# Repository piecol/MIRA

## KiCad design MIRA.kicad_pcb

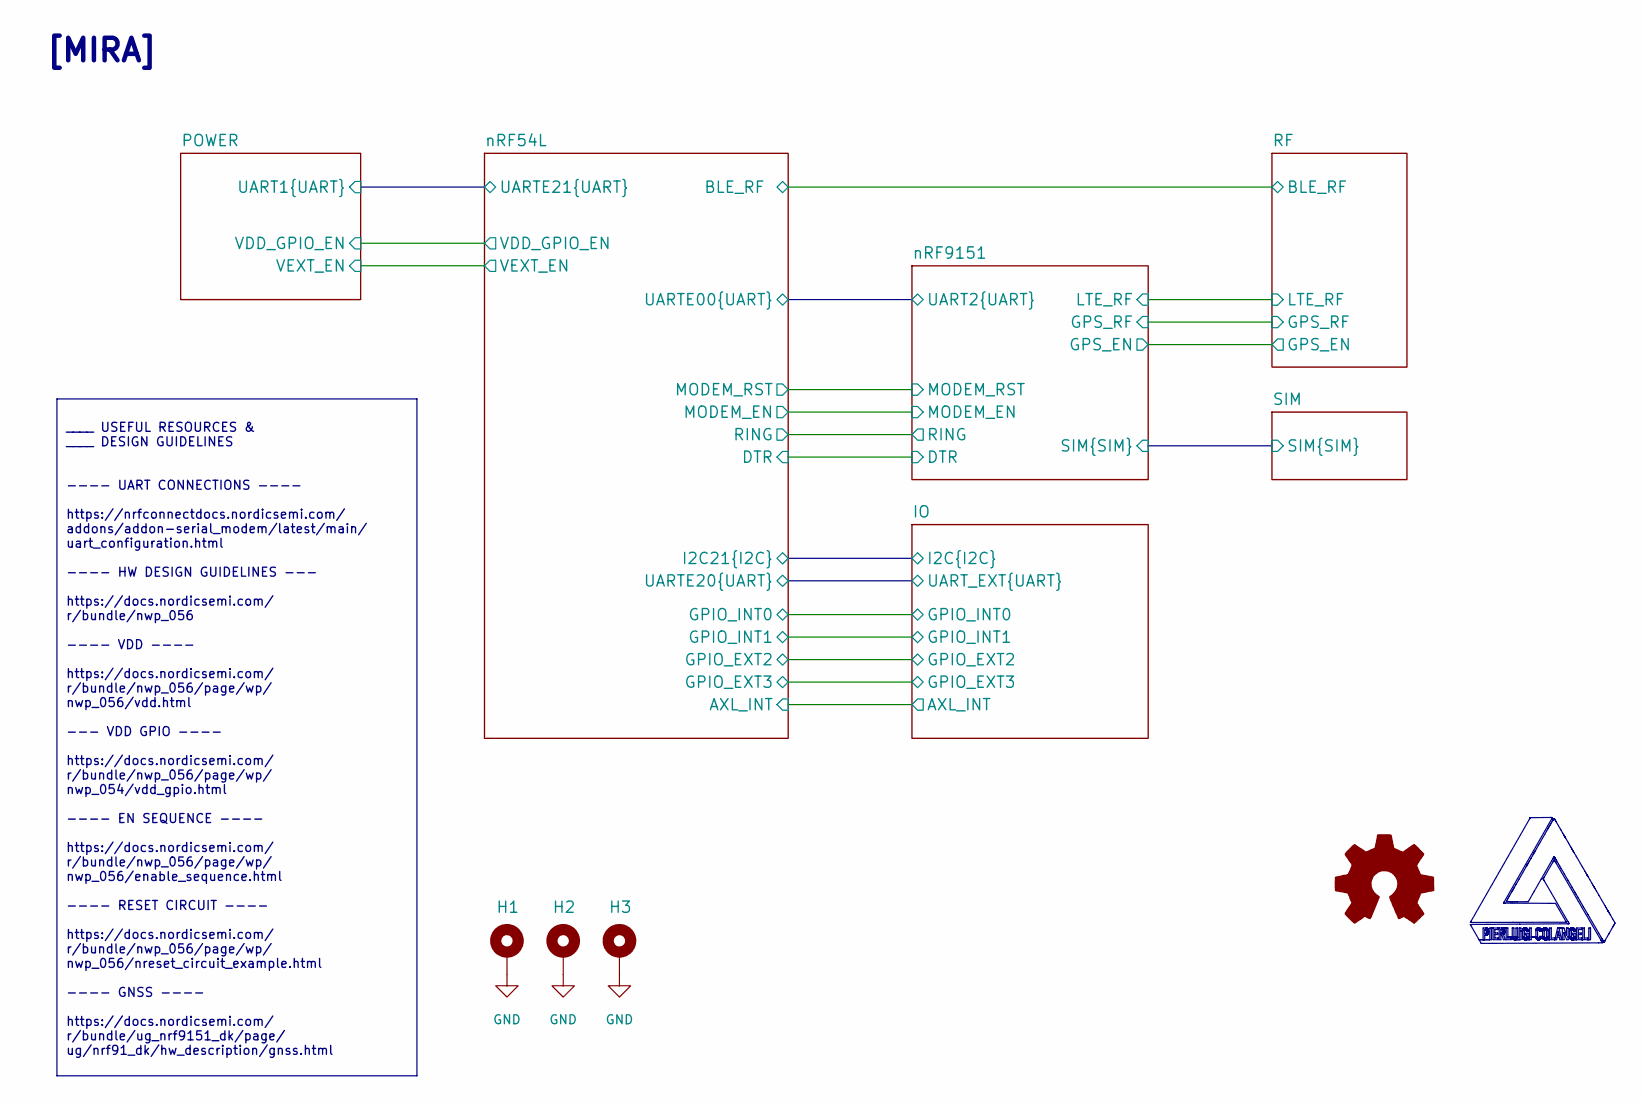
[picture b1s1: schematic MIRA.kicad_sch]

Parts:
H1, H2, H3: MountingHole_Pad; MountingHole_2.2mm_M2_ISO7380_Pad

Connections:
GND: H1.1 (1_1), H2.1 (1_1), H3.1 (1_1); also elsewhere on the board

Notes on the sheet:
[MIRA]
____ USEFUL RESOURCES & ____ DESIGN GUIDELINES ---- UART CONNECTIONS ---- https://nrfconnectdocs.nordicsemi.com/ addons/addon-serial_modem/latest/main/ uart_configuration.html ---- HW DESIGN GUIDELINES --- https://docs.nordicsemi.com/ r/bundle/nwp_056 ---- VDD ---- https://docs.nordicsemi.com/ r/bu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

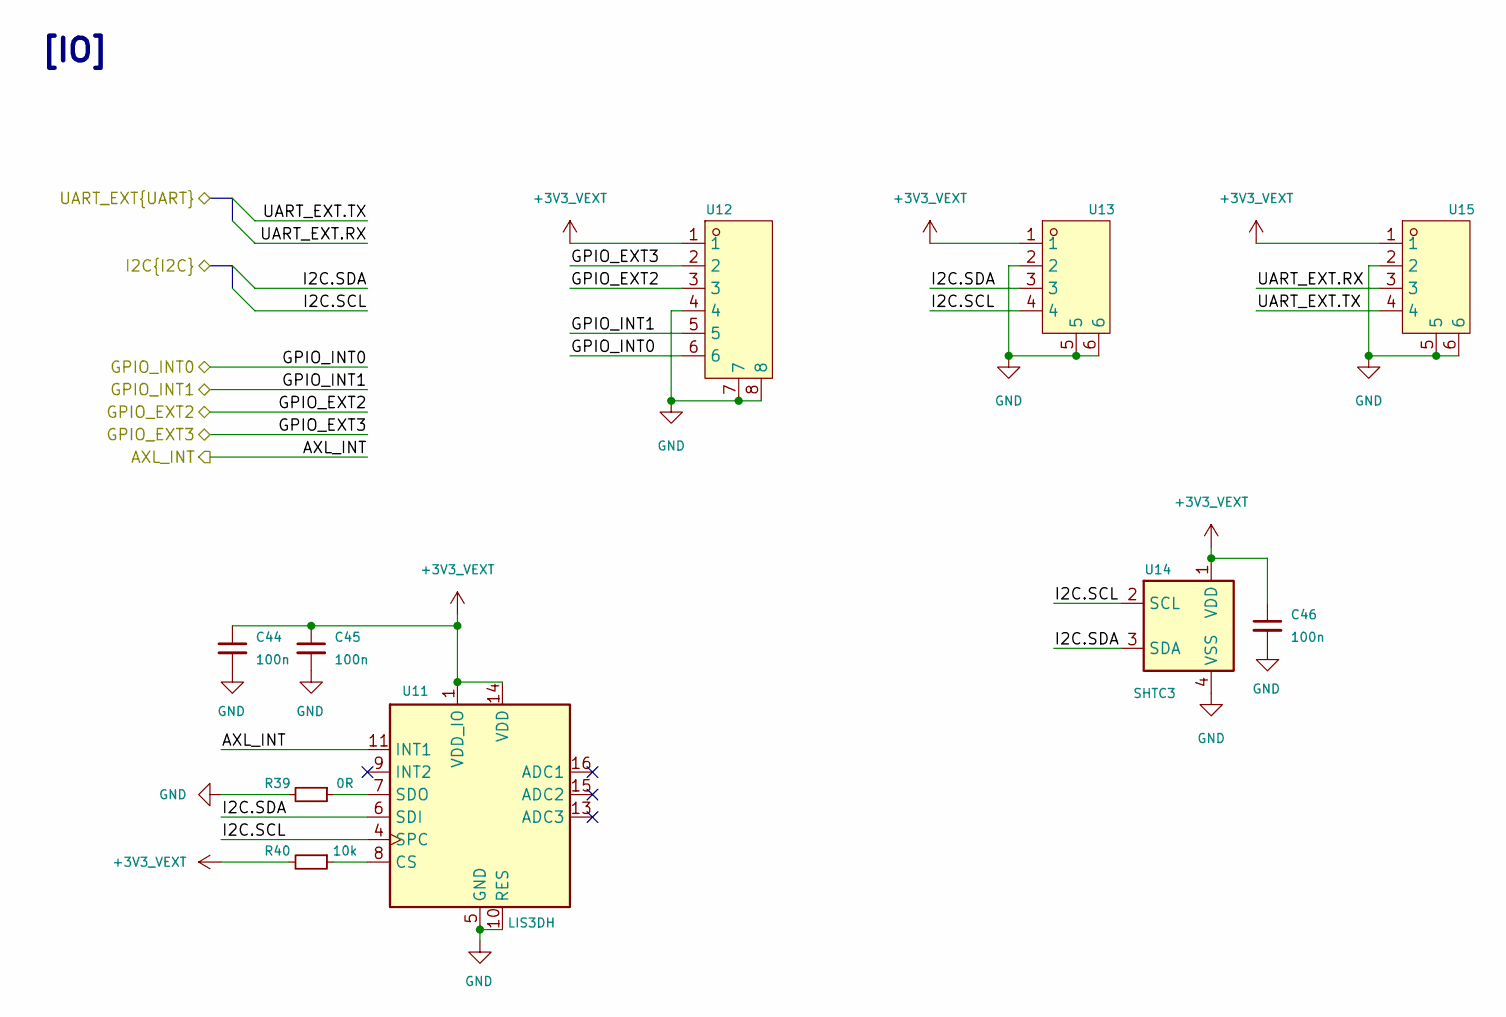
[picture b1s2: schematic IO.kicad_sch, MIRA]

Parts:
C44, C45, C46: 100n; C_0402_1005Metric; LCSC C1525
R39: 0R; R_0402_1005Metric; LCSC C17168
R40: 10k; R_0402_1005Metric; LCSC C25744
U11: LIS3DH; LGA-16_3x3mm_P0.5mm_LayoutBorder3x5y; LCSC Part C15134
U12: ZX-GH1.25-WT6; CONN-SMD_6P-P1.25_ZX-GH1.25-WT6; MPN ZX-GH1.25-WT6; LCSC Part C7429519
U13, U15: ZX-GH1.25-WT4; CONN-SMD_4P-P1.25_ZX-GH1.25-WT4; MPN ZX-GH1.25-WT4; LCSC Part C7429517
U14: SHTC3; Sensirion_DFN-4-1EP_2x2mm_P1mm_EP0.7x1.6mm; LCSC C194656

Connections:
+3V3_VEXT: C44.1, C45.1, C46.1, R40.2, U11.1 (VDD_IO), U11.14 (VDD), U12.1, U13.1, U14.1 (VDD), U15.1; also elsewhere on the board
/IO/AXL_INT: U11.11 (INT1); also elsewhere on the board
/IO/GPIO_EXT2: U12.3; also elsewhere on the board
/IO/GPIO_EXT3: U12.2; also elsewhere on the board
/IO/GPIO_INT0: U12.6; also elsewhere on the board
/IO/GPIO_INT1: U12.5; also elsewhere on the board
/IO/I2C.SCL: U11.4 (SPC), U13.4, U14.2 (SCL); also elsewhere on the board
/IO/I2C.SDA: U11.6 (SDI), U13.3, U14.3 (SDA); also elsewhere on the board
/IO/UART_EXT.RX: U15.3; also elsewhere on the board
/IO/UART_EXT.TX: U15.4; also elsewhere on the board
GND: C44.2, C45.2, C46.2, R39.2, U11.5 (GND), U11.10 (RES), U11.12 (GND), U12.4, U12.7, U12.8, U13.2, U13.5, U13.6, U14.4 (VSS), U15.2, U15.5, U15.6; also elsewhere on the board
unnamed: R40.1, U11.8 (CS)
unnamed: R39.1, U11.7 (SDO)

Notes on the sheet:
[IO]

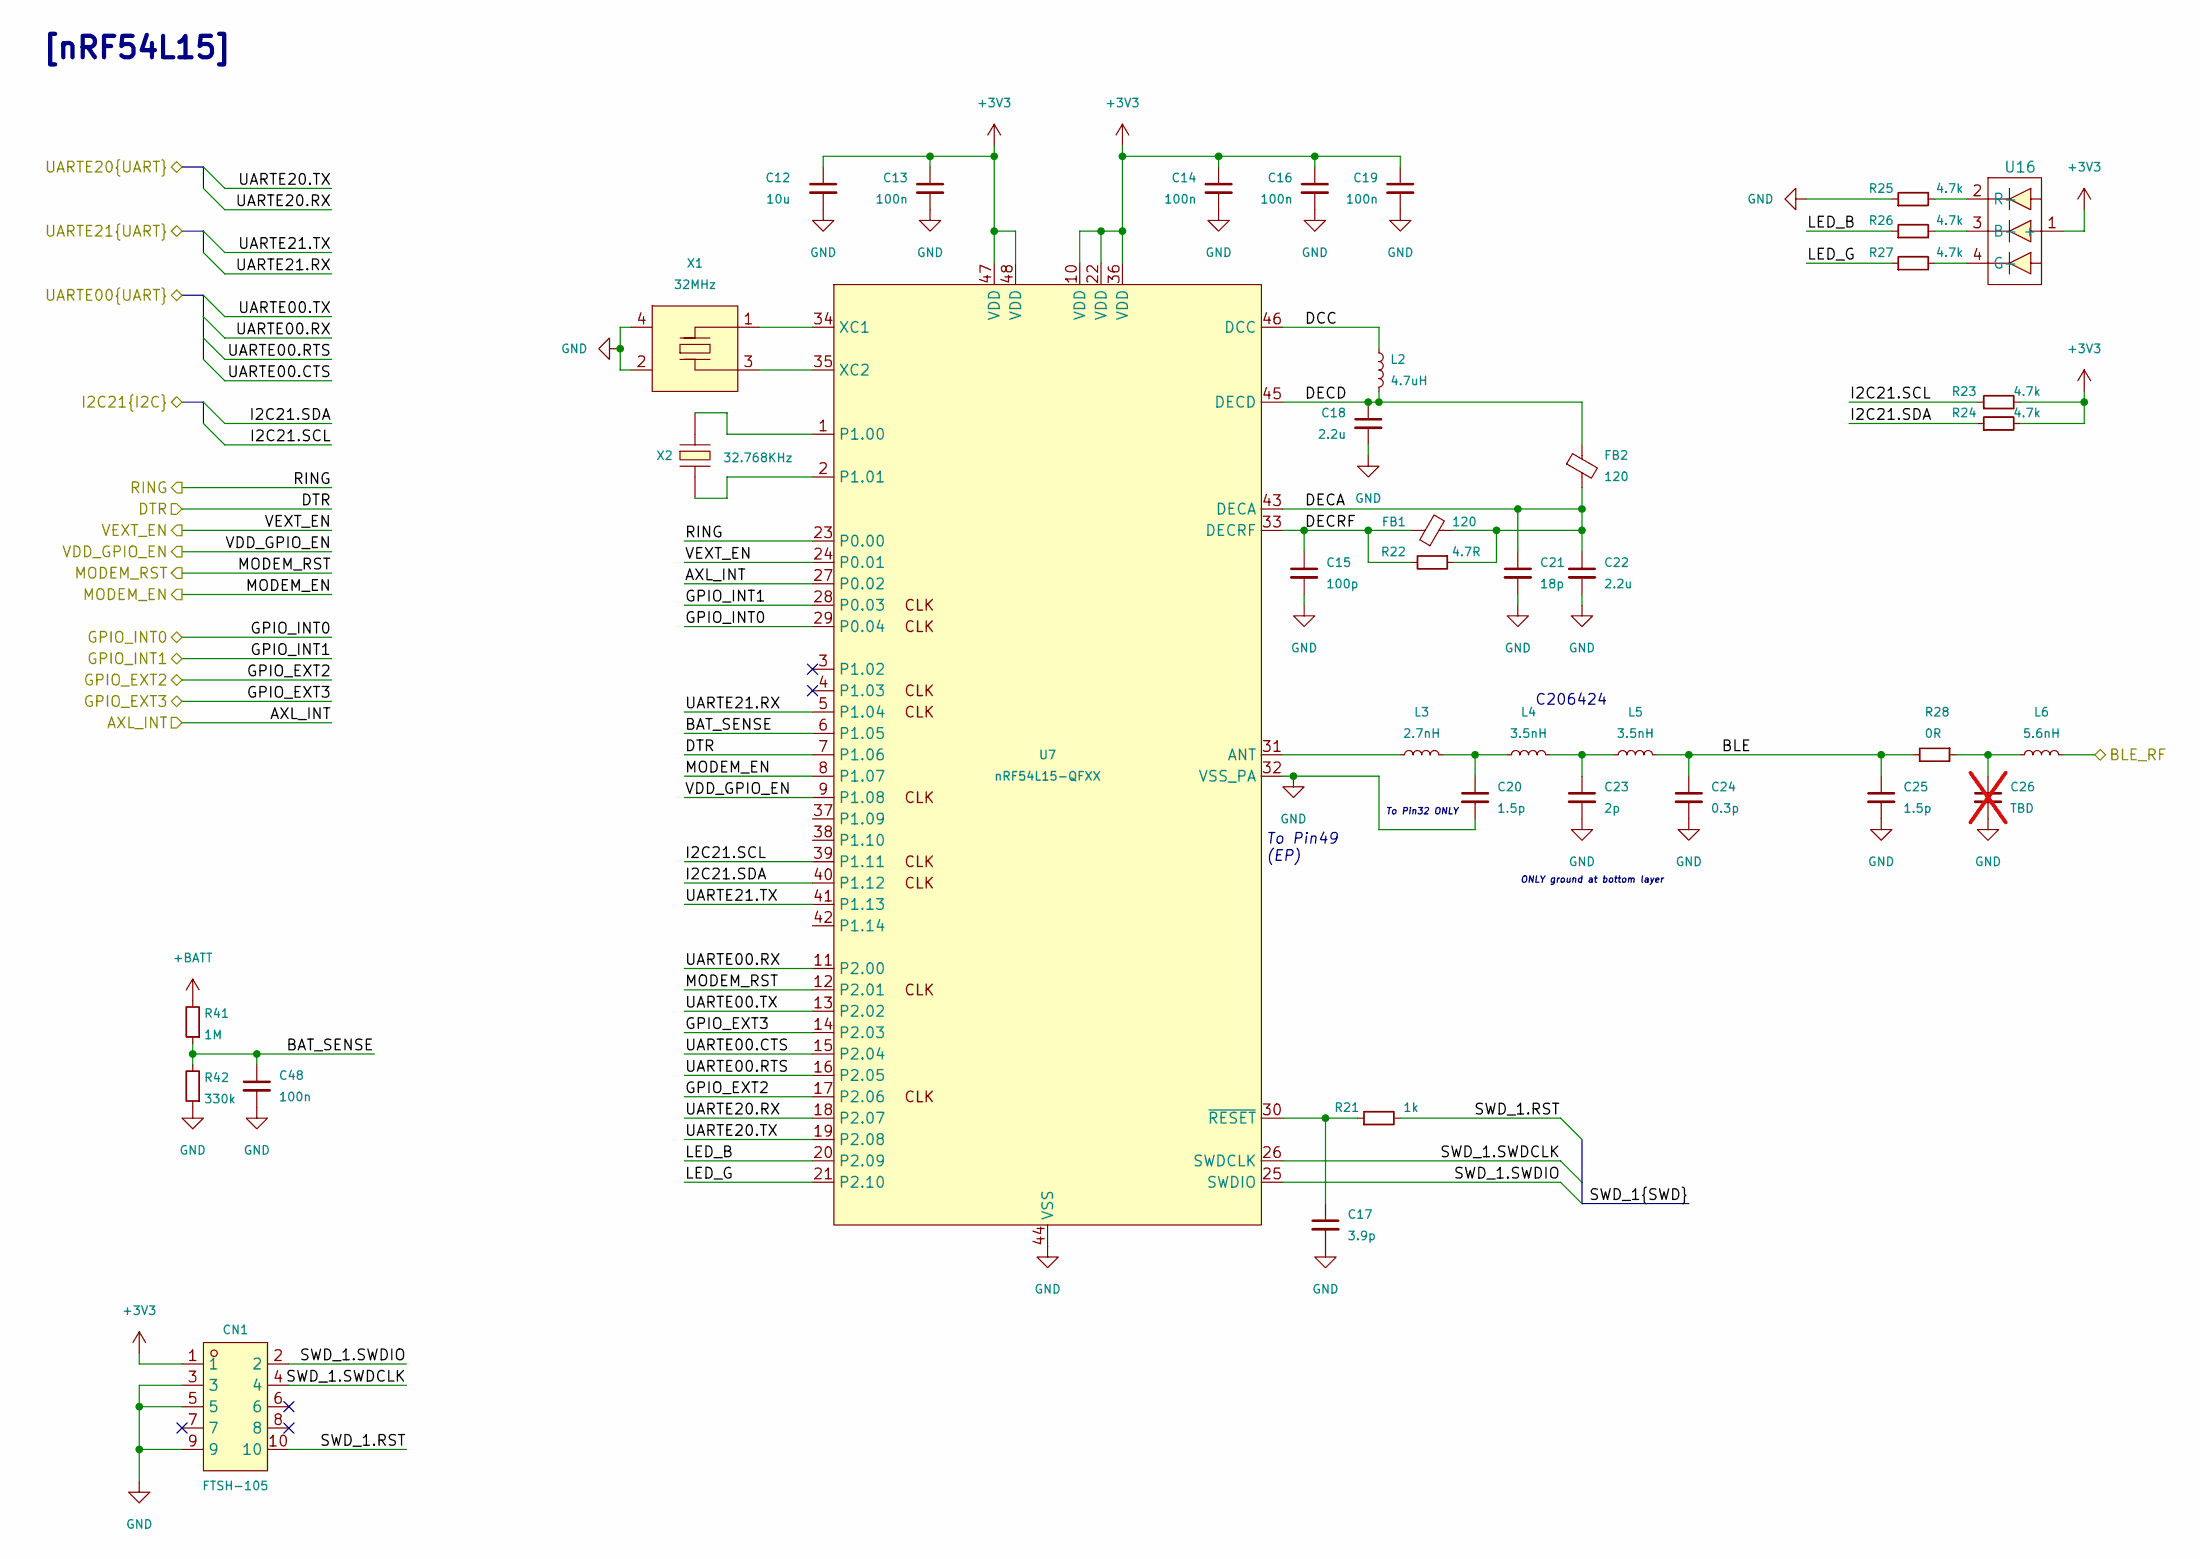
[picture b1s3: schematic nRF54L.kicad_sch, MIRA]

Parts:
C12: 10u; C_0402_1005Metric; LCSC C15525
C13, C14, C16, C19, C48: 100n; C_0201_0603Metric; LCSC C49062
C15: 100p; C_0201_0603Metric; LCSC C76917
C17: 3.9p; C_0201_0603Metric; LCSC C76926
C18, C22: 2.2u; C_0201_0603Metric; LCSC C318539
C20: 1.5p; C_0201_0603Metric; LCSC C88913
C21: 18p; C_0201_0603Metric; LCSC C161374
C23: 2p; C_0201_0603Metric; LCSC C668326
C24: 0.3p; C_0201_0603Metric; LCSC C76927
C25: 1.5p; C_0402_1005Metric; LCSC C76901
C26: TBD; C_0402_1005Metric; not fitted
CN1: FTSH-105; CONN-SMD_FTSH-105-01-L-DV-K-TR; LCSC Part C448647
FB1, FB2: 120; L_0201_0603Metric; LCSC C97850
L2: 4.7uH; L_0603_1608Metric; LCSC C76799
L3: 2.7nH; L_0201_0603Metric; LCSC C7216765
L4, L5: 3.5nH; L_0201_0603Metric; LCSC C206424
L6: 5.6nH; L_0402_1005Metric; LCSC C85670
R21: 1k; R_0402_1005Metric; LCSC C11702
R22: 4.7R; R_0402_1005Metric; LCSC C25121
R23, R24, R25, R26, R27: 4.7k; R_0402_1005Metric; LCSC C25900
R28: 0R; R_0402_1005Metric; LCSC C17168
R41: 1M; R_0402_1005Metric; LCSC C26083
R42: 330k; R_0402_1005Metric; LCSC C25778
U7: nRF54L15-QFXX; QFN-48-1EP_6x6mm_P0.4mm_EP4.6x4.6mm; LCSC C42458750
U16: APHF1608LSEEQBDZGKC; LED-SMD_4P-L1.6-W0.8_APHF1608LSEEQBDZGKC; MPN APHF1608LSEEQBDZGKC; LCSC Part C3019171
X1: 32MHz; CRYSTAL-SMD_4P-L1.6-W1.2-BL; LCSC Part C655046
X2: 32.768KHz; Crystal_SMD_MicroCrystal_CM9V-T1A-2Pin_1.6x1.0mm; LCSC Part C596929

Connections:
+3V3: C12.1, C13.1, C14.1, C16.1, C19.1, CN1.1, R23.2, R24.2, U7.10 (VDD), U7.22 (VDD), U7.36 (VDD), U7.47 (VDD), U7.48 (VDD), U16.1 (+); also elsewhere on the board
+BATT: R41.2; also elsewhere on the board
/IO/AXL_INT: U7.27 (P0.02); also elsewhere on the board
/IO/GPIO_EXT2: U7.17 (P2.06); also elsewhere on the board
/IO/GPIO_EXT3: U7.14 (P2.03); also elsewhere on the board
/IO/GPIO_INT0: U7.29 (P0.04); also elsewhere on the board
/IO/GPIO_INT1: U7.28 (P0.03); also elsewhere on the board
/IO/I2C.SCL: R23.1, U7.39 (P1.11); also elsewhere on the board
/IO/I2C.SDA: R24.1, U7.40 (P1.12); also elsewhere on the board
/IO/UART_EXT.RX: U7.18 (P2.07); also elsewhere on the board
/IO/UART_EXT.TX: U7.19 (P2.08); also elsewhere on the board
/POWER/UART1.RX: U7.5 (P1.04); also elsewhere on the board
/POWER/UART1.TX: U7.41 (P1.13); also elsewhere on the board
/RF/BLE_RF: L6.2; also elsewhere on the board
/nRF54L/BAT_SENSE: C48.1, R41.1, R42.2, U7.6 (P1.05)
/nRF54L/BLE: C24.1, C25.1, L5.2, R28.2
/nRF54L/DCC: L2.1, U7.46 (DCC)
/nRF54L/DECA: C21.1, C22.1, FB1.2, FB2.2, R22.1, U7.43 (DECA)
/nRF54L/DECD: C18.1, FB2.1, L2.2, U7.45 (DECD)
/nRF54L/DECRF: C15.1, FB1.1, R22.2, U7.33 (DECRF)
/nRF54L/DTR: U7.7 (P1.06); also elsewhere on the board
/nRF54L/LED_B: R26.1, U7.20 (P2.09)
/nRF54L/LED_G: R27.1, U7.21 (P2.10)
/nRF54L/MODEM_EN: U7.8 (P1.07); also elsewhere on the board
/nRF54L/MODEM_RST: U7.12 (P2.01); also elsewhere on the board
/nRF54L/RING: U7.23 (P0.00); also elsewhere on the board
/nRF54L/SWD_1.RST: CN1.10, R21.2
/nRF54L/SWD_1.SWDCLK: CN1.4, U7.26 (SWDCLK)
/nRF54L/SWD_1.SWDIO: CN1.2, U7.25 (SWDIO)
/nRF54L/UARTE00.CTS: U7.15 (P2.04); also elsewhere on the board
/nRF54L/UARTE00.RTS: U7.16 (P2.05); also elsewhere on the board
/nRF54L/UARTE00.RX: U7.11 (P2.00); also elsewhere on the board
/nRF54L/UARTE00.TX: U7.13 (P2.02); also elsewhere on the board
/nRF54L/VDD_GPIO_EN: U7.9 (P1.08); also elsewhere on the board
/nRF54L/VEXT_EN: U7.24 (P0.01); also elsewhere on the board
GND: C12.2, C13.2, C14.2, C15.2, C16.2, C17.2, C18.2, C19.2, C20.2, C21.2, C22.2, C23.2, C24.2, C25.2, C26.2, C48.2, CN1.3, CN1.5, CN1.9, R25.1, R42.1, U7.32 (VSS_PA), U7.44 (VSS), U7.49 (VSS), X1.2 (GND), X1.4 (GND); also elsewhere on the board
unnamed: C20.1, L3.2, L4.1
unnamed: C23.1, L4.2, L5.1
unnamed: C26.1, L6.1, R28.1
unnamed: L3.1, U7.31 (ANT)
unnamed: U7.1 (P1.00), X2.1
unnamed: U7.2 (P1.01), X2.2
unnamed: U7.34 (XC1), X1.1
unnamed: U7.35 (XC2), X1.3
unnamed: C17.1, R21.1, U7.30 (~RESET)
unnamed: R26.2, U16.3 (B-)
unnamed: R27.2, U16.4 (G-)
unnamed: R25.2, U16.2 (R-)

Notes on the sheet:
To Pin49 (EP)
C206424
[nRF54L15]
ONLY ground at bottom layer
To Pin32 ONLY

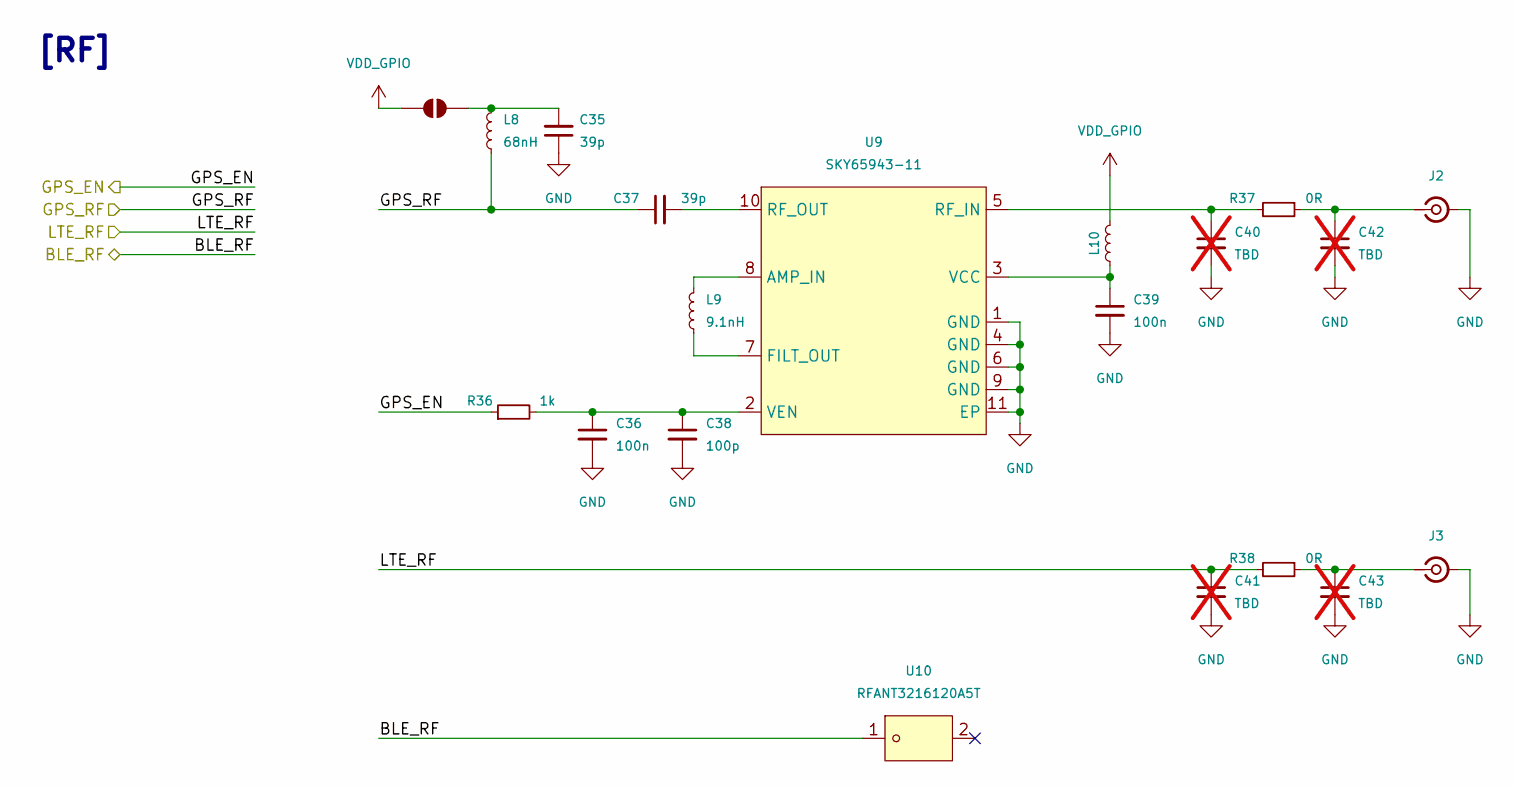
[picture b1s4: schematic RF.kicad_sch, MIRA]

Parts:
C35, C37: 39p; C_0402_1005Metric; LCSC C1563
C36, C39: 100n; C_0402_1005Metric; LCSC C1525
C38: 100p; C_0201_0603Metric; LCSC C76917
C40, C41, C42, C43: TBD; C_0402_1005Metric; not fitted
J2, J3: Conn_Coaxial_Small; U.FL_Molex_MCRF_73412-0110_Vertical; LCSC C22418213
JP8: SolderJumper_2_Open; SolderJumper_Mini
L8: 68nH; L_0402_1005Metric; LCSC Part C108965
L9: 9.1nH; L_0402_1005Metric; LCSC Part C113122
L10: BLM15PX121SN1D; L_0402_1005Metric; LCSC Part C88970
R36: 1k; R_0402_1005Metric; LCSC C11702
R37, R38: 0R; R_0402_1005Metric; LCSC C17168
U9: SKY65943-11; MCM-10_L2.5-W2.5-P0.50-BL-EP; MPN SKY65943-11; LCSC Part C2654442
U10: RFANT3216120A5T; FILTER-SMD_1206-2P-L3.2-W1.6-L; LCSC Part C127629

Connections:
/RF/BLE_RF: U10.1 (1_1); also elsewhere on the board
/RF/GPS_EN: R36.1; also elsewhere on the board
/RF/GPS_RF: C37.1, L8.1; also elsewhere on the board
/RF/LTE_RF: C41.1, R38.2; also elsewhere on the board
GND: C35.1, C36.2, C38.2, C39.2, C40.2, C41.2, C42.2, C43.2, J2.2 (Ext), J3.2 (Ext), U9.1 (GND), U9.4 (GND), U9.6 (GND), U9.9 (GND), U9.11 (EP); also elsewhere on the board
unnamed: C42.1, J2.1 (In), R37.1
unnamed: C43.1, J3.1 (In), R38.1
unnamed: C35.2, JP8.1 (A), L8.2
unnamed: L9.2, U9.8 (AMP_IN)
unnamed: L9.1, U9.7 (FILT_OUT)
unnamed: C40.1, R37.2, U9.5 (RF_IN)
unnamed: C37.2, U9.10 (RF_OUT)
unnamed: C39.1, L10.1, U9.3 (VCC)
unnamed: C36.1, C38.1, R36.2, U9.2 (VEN)
VDD_GPIO: JP8.2 (B), L10.2; also elsewhere on the board

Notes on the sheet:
[RF]

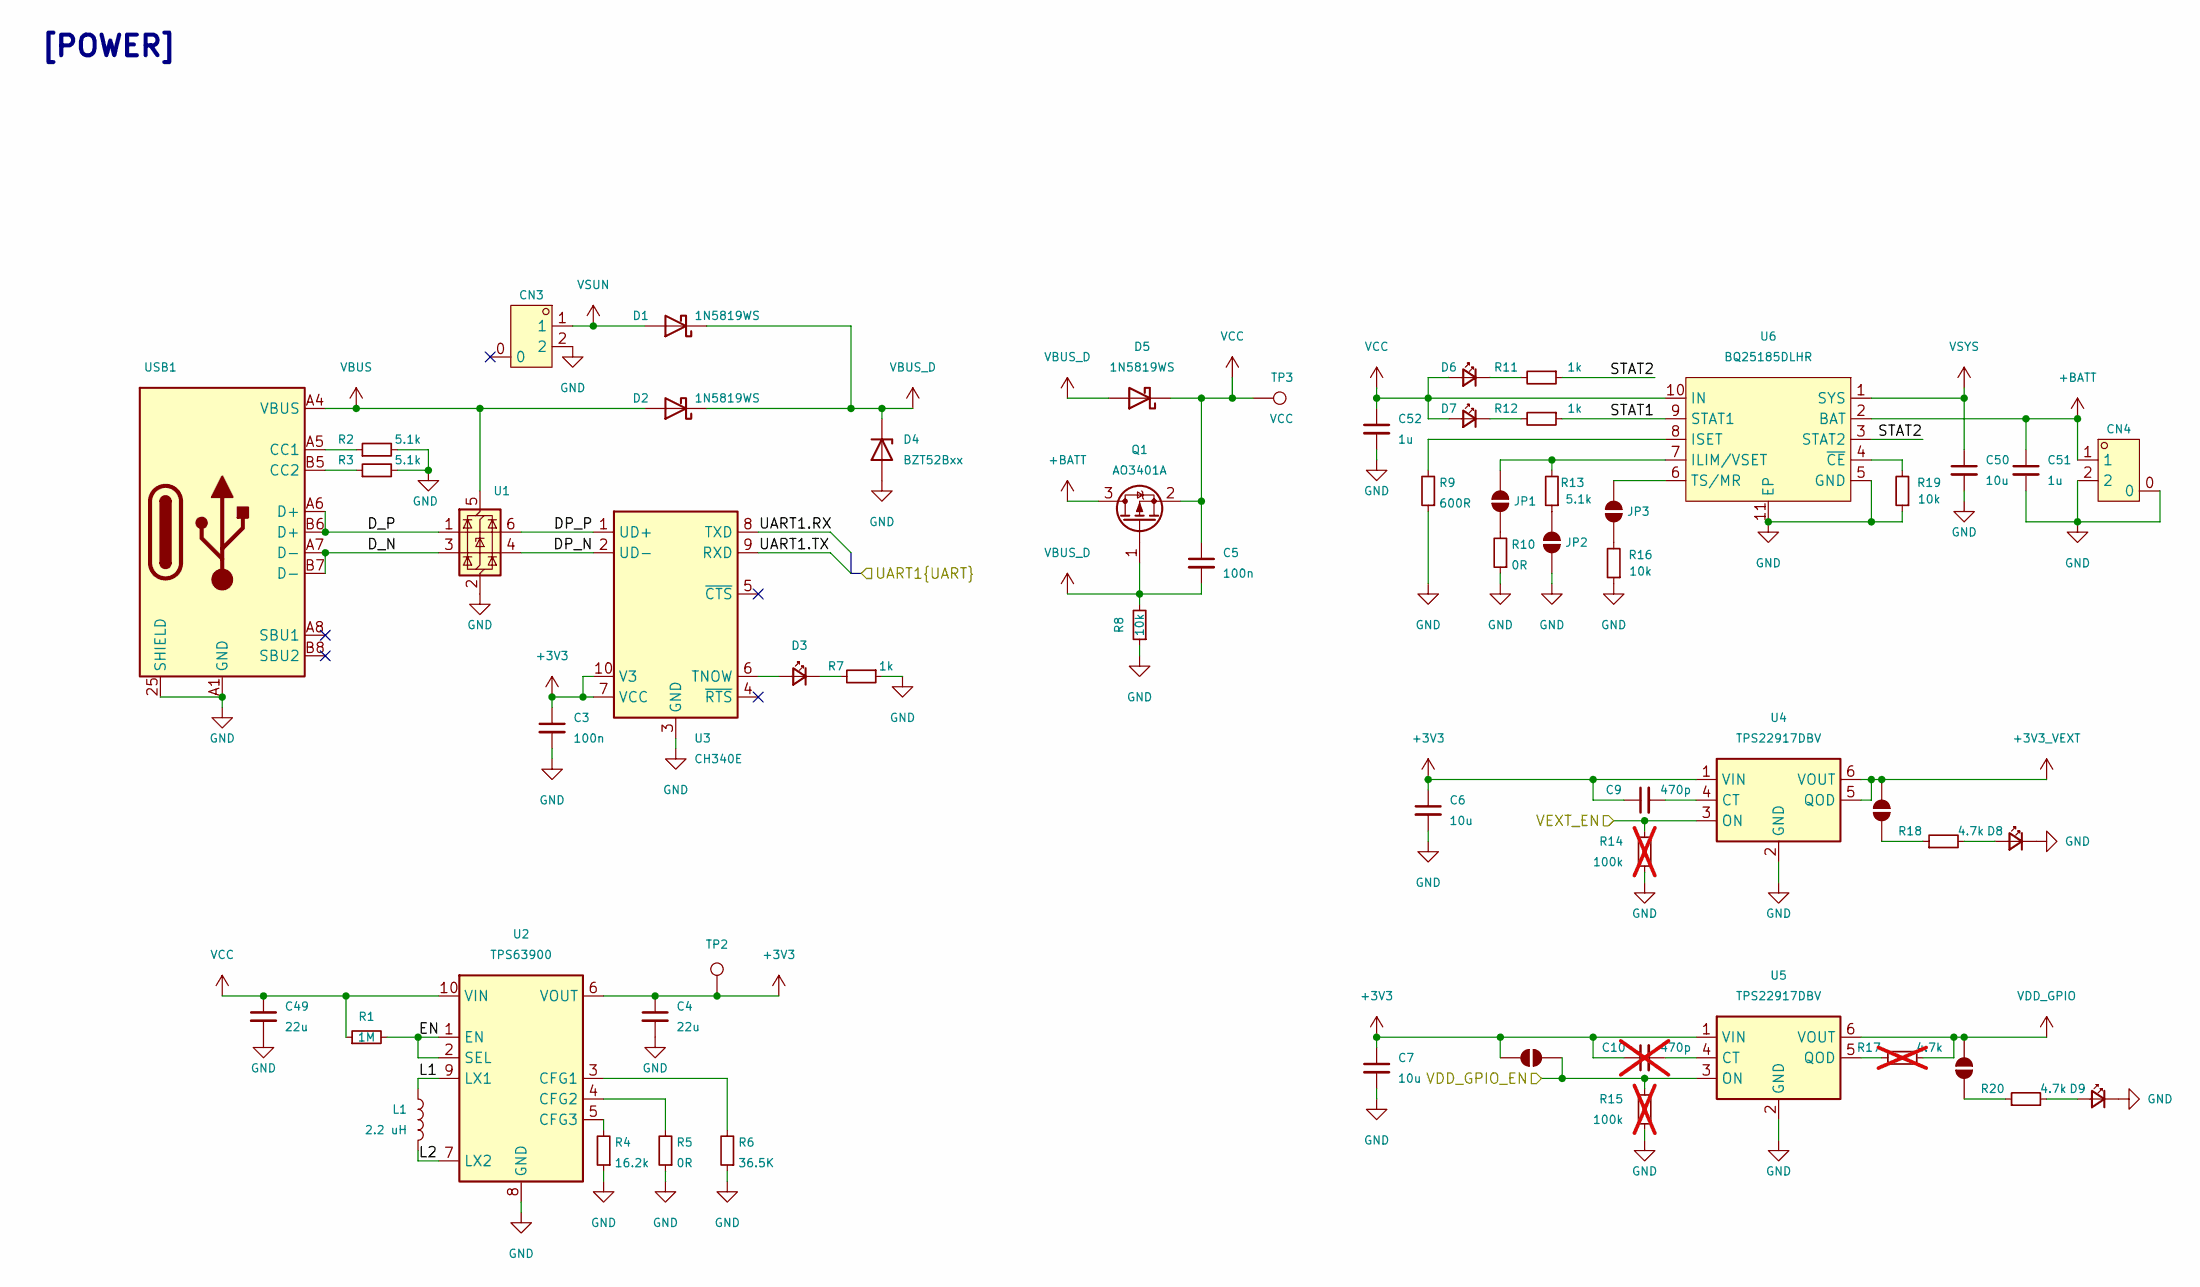
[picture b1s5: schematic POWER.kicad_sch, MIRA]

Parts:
C3, C5: 100n; C_0402_1005Metric; LCSC C1525
C4, C49: 22u; C_0805_2012Metric; LCSC C45783
C6, C7, C50: 10u; C_0402_1005Metric; LCSC C15525
C9: 470p; C_0402_1005Metric; LCSC C76971
C10: 470p; C_0402_1005Metric; LCSC C76971; not fitted
C51, C52: 1u; C_0402_1005Metric; LCSC C52923
CN3, CN4: 1.25mm-2P socket; CONN-SMD_1.25T-2P; MPN 1.25T-2P立贴; LCSC Part C43462
D1, D2, D5: 1N5819WS; D_SOD-323; LCSC C191023
D3, D6, D7, D8, D9: XL-1005UBC_C22355736; LED_0402_1005Metric; MPN XL-1005UBC; LCSC Part C22355736
D4: BZT52Bxx; D_SOD-123F; LCSC C52148463
JP1, JP2, JP3, JP4, JP5, JP9: SolderJumper_2_Open; SolderJumper_Mini
L1: 2.2 uH; L_Coilcraft_XxL4020; LCSC C3151182
Q1: AO3401A; SOT-23; LCSC C15127
R1: 1M; R_0402_1005Metric; LCSC C26083
R2, R3, R13: 5.1k; R_0402_1005Metric; MPN 0402WGF5101TCE; LCSC Part C25905
R4: 16.2k; R_0402_1005Metric; LCSC C27176
R5, R10: 0R; R_0402_1005Metric; LCSC C17168
R6: 36.5K; R_0402_1005Metric; LCSC C25887
R7, R11, R12: 1k; R_0402_1005Metric; LCSC C11702
R8, R16, R19: 10k; R_0402_1005Metric; LCSC C25744
R9: 600R; R_0402_1005Metric; LCSC C4961
R14, R15: 100k; R_0402_1005Metric; LCSC C25741; not fitted
R17: 4.7k; R_0402_1005Metric; LCSC C25900; not fitted
R18, R20: 4.7k; R_0402_1005Metric; LCSC C25900
TP2: TestPoint; TestPoint_Pad_D1.0mm
TP3: VCC; TestPoint_Pad_D1.5mm
U1: USBLC6-2P6; SOT-666-6_L1.6-W1.2-P0.50-LS1.6-BL; MPN TPUSBLC6-2P6; LCSC Part C2682291
U2: TPS63900; WSON-10-1EP_2.5x2.5mm_P0.5mm_EP1.2x2mm_ThermalVias; LCSC C1518762
U3: CH340E; MSOP-10_3x3mm_P0.5mm; LCSC C99652
U4, U5: TPS22917DBV; SOT-23-6; LCSC C2681320
U6: BQ25185DLHR; WSON-10_L2.2-W2.0-P0.40-BL-EP_TI_DLH0010A; MPN BQ25185DLHR; LCSC Part C19725033
USB1: HC-TYPE-C-16P-01M; USB-C-SMD_HCTL_HC-TYPE-C-16P-01M; MPN HC-TYPE-C-16P-01M; LCSC Part C2894899

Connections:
+3V3: C3.1, C4.1, C6.1, C7.1, C9.1, C10.1, JP9.2 (B), TP2.1 (1_1), U2.6 (VOUT), U3.7 (VCC), U3.10 (V3), U4.1 (VIN), U5.1 (VIN); also elsewhere on the board
+3V3_VEXT: JP4.2 (B), U4.5 (QOD), U4.6 (VOUT); also elsewhere on the board
+BATT: C51.1, CN4.1, Q1.3 (D), U6.2 (BAT); also elsewhere on the board
/POWER/DP_N: U1.4 (I/O2), U3.2 (UD-)
/POWER/DP_P: U1.6 (I/O1), U3.1 (UD+)
/POWER/D_N: U1.3 (I/O2), USB1.A7 (D-), USB1.B7 (D-)
/POWER/D_P: U1.1 (I/O1), USB1.A6 (D+), USB1.B6 (D+)
/POWER/EN: R1.2, U2.1 (EN), U2.2 (SEL)
/POWER/L1: L1.1, U2.9 (LX1)
/POWER/L2: L1.2, U2.7 (LX2)
/POWER/STAT1: R12.1, U6.9 (STAT1)
/POWER/STAT2: R11.1, U6.3 (STAT2)
/POWER/UART1.RX: U3.8 (TXD); also elsewhere on the board
/POWER/UART1.TX: U3.9 (RXD); also elsewhere on the board
/nRF54L/VDD_GPIO_EN: JP9.1 (A), R15.2, U5.3 (ON); also elsewhere on the board
/nRF54L/VEXT_EN: R14.2, U4.3 (ON); also elsewhere on the board
GND: C3.2, C4.2, C6.2, C7.2, C49.2, C50.2, C51.2, C52.2, CN3.2, CN4.0, CN4.2, D4.2 (A), D8.1 (K), D9.1 (K), JP2.1 (A), R2.2, R3.2, R4.1, R5.1, R6.1, R7.1, R8.1, R9.1, R10.1, R14.1, R15.1, R16.1, R19.1, U1.2 (GND), U2.8 (GND), U2.11 (GND), U3.3 (GND), U4.2 (GND), U5.2 (GND), U6.5 (GND), U6.11 (EP), USB1.25 (SHIELD), USB1.26 (SHIELD), USB1.27 (SHIELD), USB1.28 (SHIELD), USB1.A1 (GND), USB1.A12 (GND), USB1.B1 (GND), USB1.B12 (GND); also elsewhere on the board
unnamed: D3.2 (A), U3.6 (TNOW)
unnamed: D3.1 (K), R7.2
unnamed: D6.1 (K), R11.2
unnamed: D7.1 (K), R12.2
unnamed: D8.2 (A), R18.2
unnamed: D9.2 (A), R20.2
unnamed: JP1.1 (A), R10.2
unnamed: JP1.2 (B), R13.2, U6.7 (ILIM/VSET)
unnamed: JP2.2 (B), R13.1
unnamed: JP3.1 (A), R16.2
unnamed: JP3.2 (B), U6.6 (TS/MR)
unnamed: JP4.1 (A), R18.1
unnamed: JP5.1 (A), R20.1
unnamed: R6.2, U2.3 (CFG1)
unnamed: R5.2, U2.4 (CFG2)
unnamed: R4.2, U2.5 (CFG3)
unnamed: C9.2, U4.4 (CT)
unnamed: C10.2, U5.4 (CT)
unnamed: R17.1, U5.5 (QOD)
unnamed: R9.2, U6.8 (ISET)
unnamed: R19.2, U6.4 (~CE)
unnamed: R2.1, USB1.A5 (CC1)
unnamed: R3.1, USB1.B5 (CC2)
VBUS: D2.2 (A), U1.5 (VBUS), USB1.A4 (VBUS), USB1.A9 (VBUS), USB1.B4 (VBUS), USB1.B9 (VBUS)
VBUS_D: C5.2, D1.1 (K), D2.1 (K), D4.1 (K), D5.2 (A), Q1.1 (G), R8.2
VCC: C5.1, C49.1, C52.1, D5.1 (K), D6.2 (A), D7.2 (A), Q1.2 (S), R1.1, TP3.1 (1_1), U2.10 (VIN), U6.10 (IN)
VDD_GPIO: JP5.2 (B), R17.2, U5.6 (VOUT); also elsewhere on the board
VSUN: CN3.1, D1.2 (A)
VSYS: C50.1, U6.1 (SYS); also elsewhere on the board

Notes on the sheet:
[POWER]

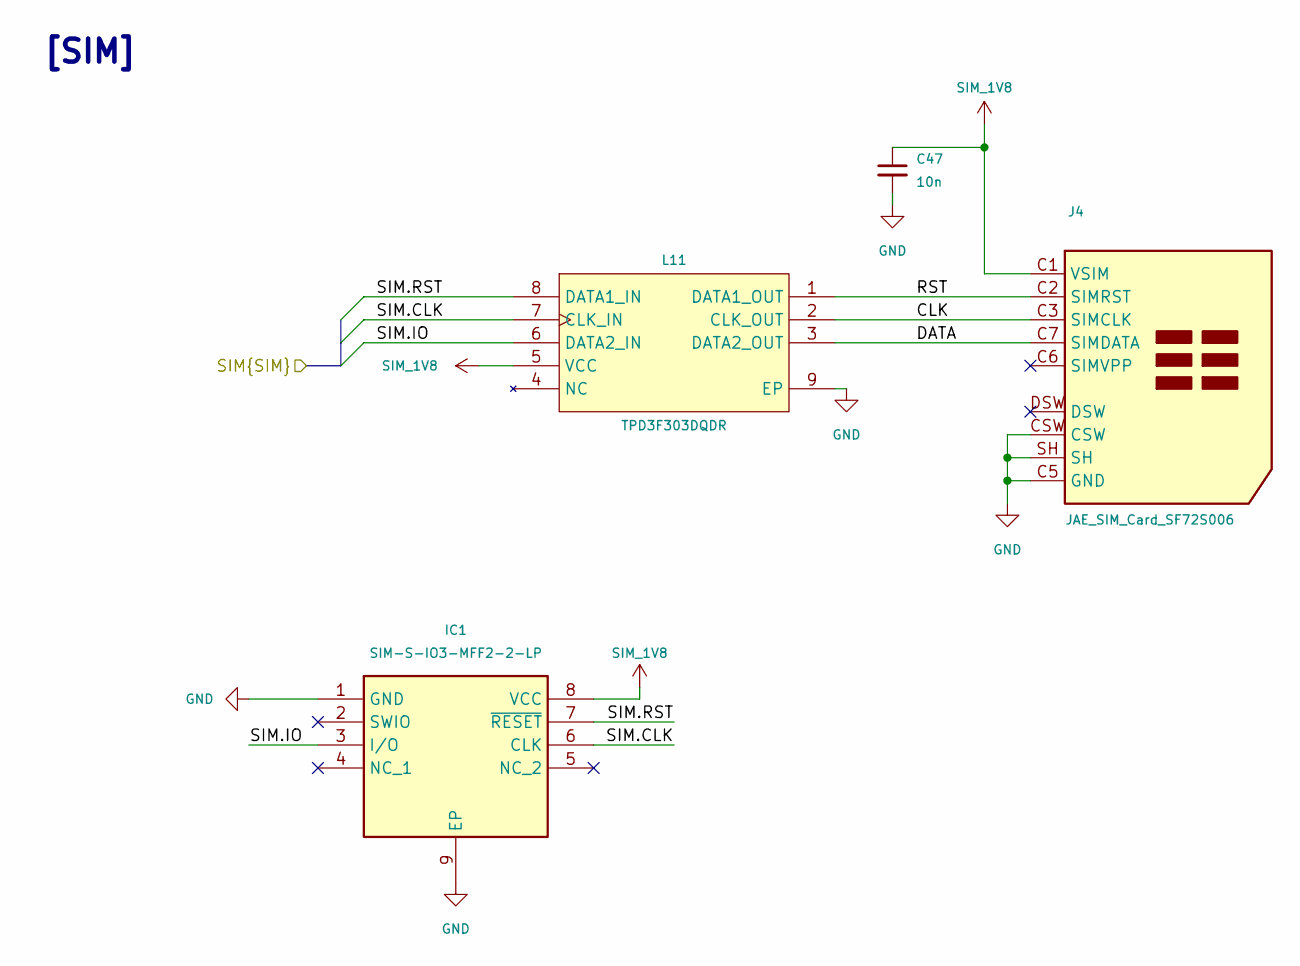
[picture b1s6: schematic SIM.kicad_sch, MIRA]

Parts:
C47: 10n; C_0402_1005Metric; LCSC C15195
IC1: SIM-S-IO3-MFF2-2-LP; SON127P600X500X100-9N-D; Manufacturer_Part_Number SIM-S-IO3-MFF2-2-LP; Mouser Part Number 57-SIM-S-IO3-MFF22LP
J4: JAE_SIM_Card_SF72S006; LCSC C2977286
L11: TPD3F303DQDR; WSON-8_L1.7-W1.4-P0.40-BL-EP; LCSC Part C2869050

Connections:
/SIM/CLK: J4.C3 (SIMCLK), L11.2 (CLK_OUT)
/SIM/DATA: J4.C7 (SIMDATA), L11.3 (DATA2_OUT)
/SIM/RST: J4.C2 (SIMRST), L11.1 (DATA1_OUT)
/SIM/SIM.CLK: IC1.6 (CLK), L11.7 (CLK_IN); also elsewhere on the board
/SIM/SIM.IO: IC1.3 (I/O), L11.6 (DATA2_IN); also elsewhere on the board
/SIM/SIM.RST: IC1.7 (~RESET), L11.8 (DATA1_IN); also elsewhere on the board
GND: C47.2, IC1.1 (GND), IC1.9 (EP), J4.C5 (GND), J4.CSW, J4.SH, L11.9 (EP); also elsewhere on the board
SIM_1V8: C47.1, IC1.8 (VCC), J4.C1 (VSIM), L11.5 (VCC); also elsewhere on the board

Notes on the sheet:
[SIM]
